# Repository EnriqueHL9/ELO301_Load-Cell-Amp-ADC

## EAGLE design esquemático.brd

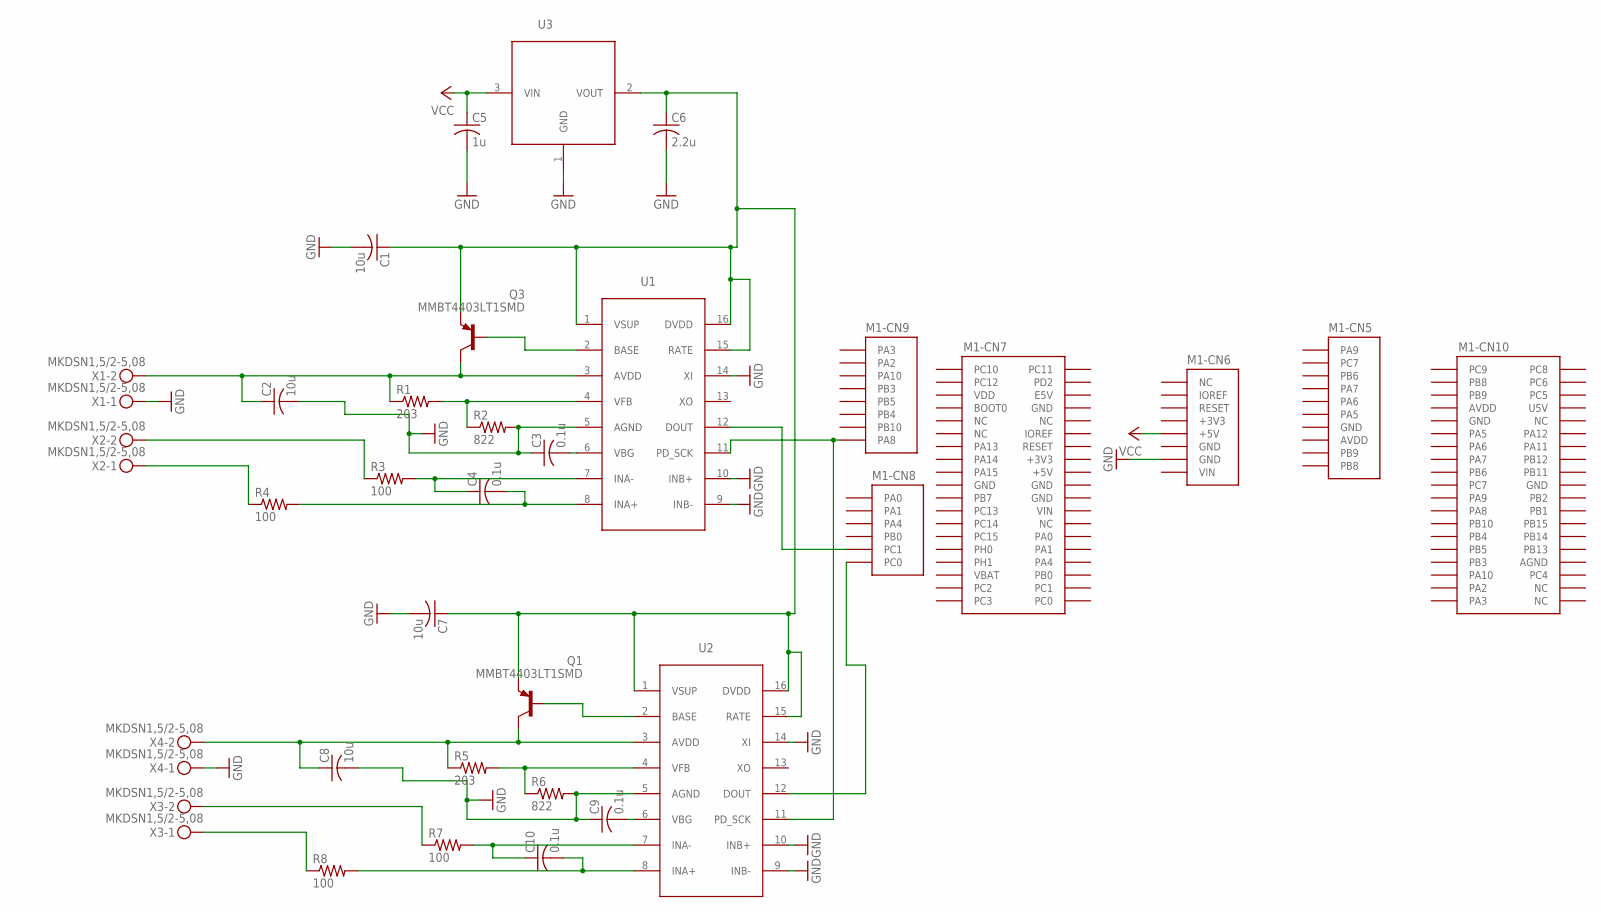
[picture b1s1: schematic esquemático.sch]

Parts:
C1, C2, C7, C8: 10u; C0805
C3, C4, C9, C10: 0.1u; C0805
C5: 1u; C0805
C6: 2.2u; C0805
M1: NUCLEO-L452RE; NUCLEO-64
Q1, Q3: MMBT4403LT1SMD; SOT23-BEC
R1, R5: 203; R0805
R2, R6: 822; R0805
R3, R4, R7, R8: 100; R0805
U1, U2: HX711SOIC127P600X140-16N; SOIC127P600X140-16N
U3: AP2210N-4.0TRG1; SOT-23-3
X1, X2, X3, X4: MKDSN1,5/2-5,08

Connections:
+3V3: M1.CN6-4 (+3V3), M1.CN7-16 (+3V3)
+5V: M1.CN7-18 (+5V)
AGND: M1.CN10-32 (AGND)
AVDD: M1.CN5-8 (AVDD), M1.CN10-7 (AVDD)
GND: C1.2, C2.2, C3.1, C5.2, C6.2, C7.2, C8.2, C9.1, M1.CN5-7 (GND), M1.CN6-6 (GND), M1.CN6-7 (GND), M1.CN7-8 (GND), M1.CN7-19 (GND), M1.CN7-20 (GND), M1.CN7-22 (GND), M1.CN10-9 (GND), M1.CN10-20 (GND), R2.2, R6.2, U1.5 (AGND), U1.9 (INB-), U1.10 (INB+), U1.14 (XI), U2.5 (AGND), U2.9 (INB-), U2.10 (INB+), U2.14 (XI), U3.1 (GND), X1.1, X4.1
IOREF: M1.CN6-2 (IOREF)
unnamed: C2.1, Q3.C, R1.1, U1.3 (AVDD), X1.2
unnamed: C4.1, R3.2, U1.7 (INA-)
unnamed: M1.CN9-8 (PA8), U1.11 (PD_SCK), U2.11 (PD_SCK)
unnamed: R1.2, R2.1, U1.4 (VFB)
unnamed: R3.1, X2.2
unnamed: C4.2, R4.2, U1.8 (INA+)
unnamed: R4.1, X2.1
unnamed: C3.2, U1.6 (VBG)
unnamed: C8.1, Q1.C, R5.1, U2.3 (AVDD), X4.2
unnamed: Q3.B, U1.2 (BASE)
unnamed: R5.2, R6.1, U2.4 (VFB)
unnamed: C10.1, R7.2, U2.7 (INA-)
unnamed: R7.1, X3.2
unnamed: C10.2, R8.2, U2.8 (INA+)
unnamed: R8.1, X3.1
unnamed: C9.2, U2.6 (VBG)
unnamed: Q1.B, U2.2 (BASE)
unnamed: M1.CN8-5 (PC1), U1.12 (DOUT)
unnamed: M1.CN8-6 (PC0), U2.12 (DOUT)
unnamed: C1.1, C6.1, C7.1, Q1.E, Q3.E, U1.1 (VSUP), U1.15 (RATE), U1.16 (DVDD), U2.1 (VSUP), U2.15 (RATE), U2.16 (DVDD), U3.2 (VOUT)
U5V: M1.CN10-8 (U5V)
VBAT: M1.CN7-33 (VBAT)
VCC: C5.1, M1.CN6-5 (+5V), U3.3 (VIN)
VDD: M1.CN7-5 (VDD)
VIN: M1.CN6-8 (VIN), M1.CN7-24 (VIN)

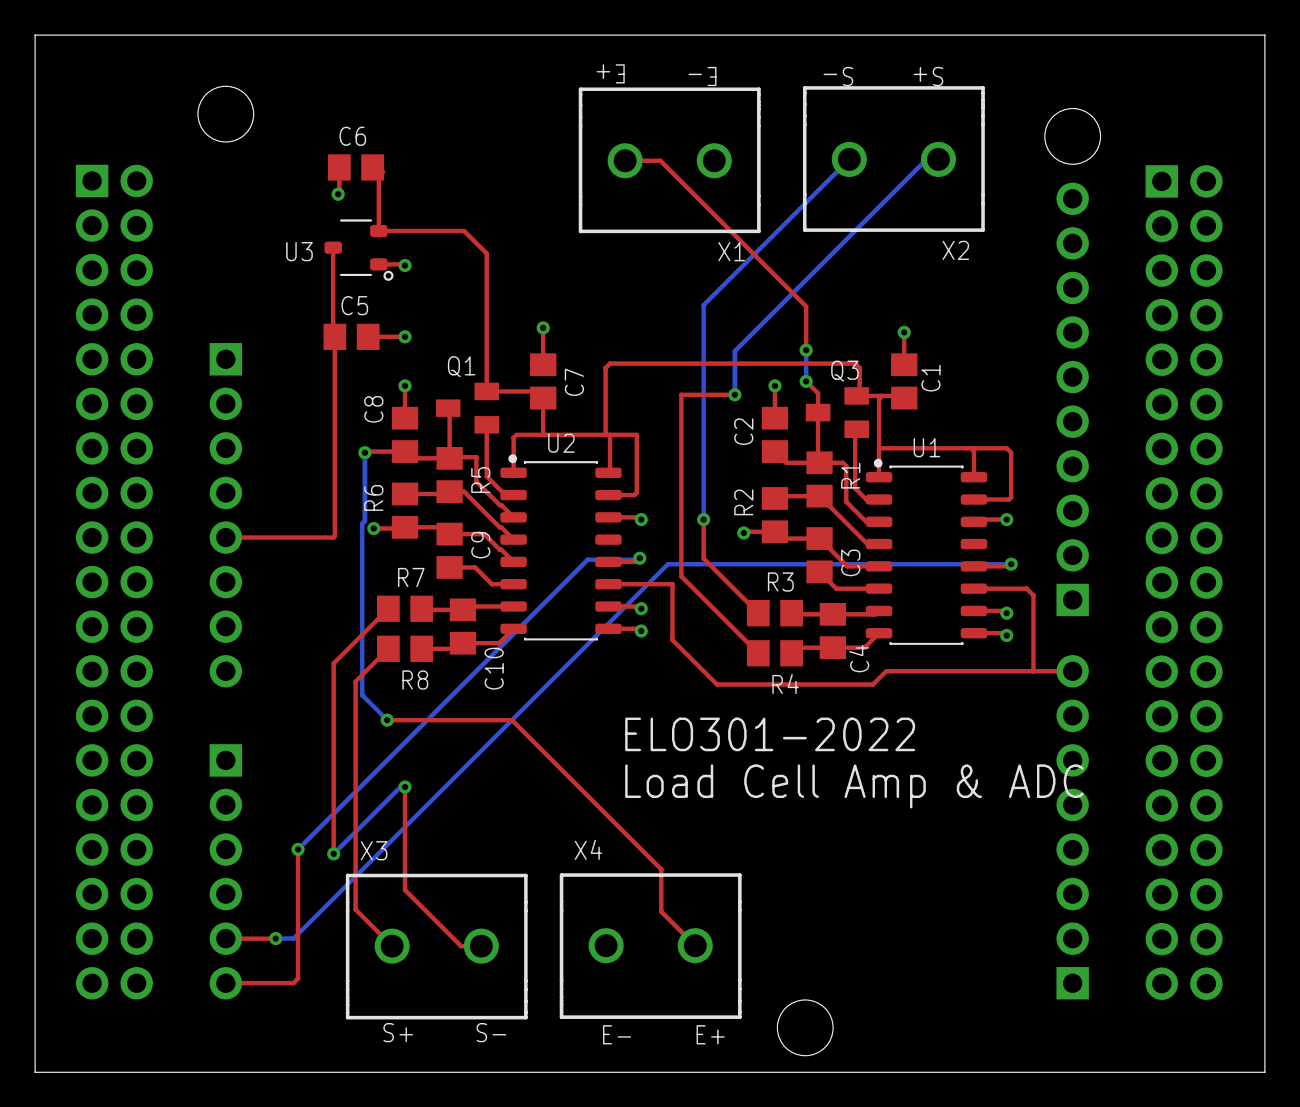
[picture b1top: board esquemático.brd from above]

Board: 2 copper layers, 70.1 x 59.1 mm, 28 parts (0 on the bottom side), 25 nets.
